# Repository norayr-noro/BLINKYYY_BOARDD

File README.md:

# BLINKYYY_BOARDD
This project is based on the stasis guide on the blinky board, where I mostly followed the guide and changed the final look of the PCB to be a FISH (a FIH if you may):

The circuit is based on the original LED chaser design using a 555 timer IC and a CD4017 decade counter. The LEDs light up sequentially, creating a moving animation around the fish-shaped board. While the electronics stay close to the original tutorial, most of the work went into redesigning the PCB layout and making the board look unique.

# Process

The project, first of all, went through the schematic stage as all projects do. It wasn't anything too interesting. For this project ill be using KiCad.  The guide used a 555 chaser and a 4017 IC, which sounds like random letters and words, but kinda makes sense if you think about it. For example, the 555 timer in this build is kinda the "brain" of the whole build, and as far as I understand, the name comes from the 3x 5K ohm internal resistance, while for the IC unit it would help me connect 10 LED's to the board with ease because it has so many pins (think of it as a "spreader" here). Other than those 2 parts, the other parts in the kit are really simple, like an LED, resistors, a polarized (+ and - differentiate in this one, so be careful when wiring!), and a normal capacitor (don't forget the potentiometer too!!).

After understanding what everything dose the next step was to wire all of them, which wasn't difficult at all, except for the wiring for the 555 timer. For context, the timer has 3 modes:
- Monostable (for time delays) mode, which is usually used as a stopwatch
- Astable Mode, which shifts between high and low
- Bistable Mode, which is like a toggle mode (eg a LED turning on and off with different buttons)
For my build, I followed the Astable mode, which has a bit of a weird wiring, but it wasn't too hard.
Also, usually when routing, I learnt it's better to label wires (by pressing A) so it's easier to understand than to wire everything in one fell swoop.
After all of that, the schematic looks a bit like this:

# The PCB 

Finally, were are onto the PCB designing. Before this, of course you first had to add footprints, obviously. Don't know what they are thinking of symbols and footprints like this, imagine a symbol, something used to understand how a part has to be routed, it's for our case, the symbols are the 555 timer, the IC... everything on the schematic that counts as a part is, and as for footprints Its how the part would look like on the real pcb itself. So I mostly did the same footprints assigning like on the guide this:(+ you will have to download the footprint from [sign in and download](https://app.ultralibrarian.com/details/15b11d40-103f-11e9-ab3a-0a3560a4cccc/Texas-Instruments/CD4017BE]) )

After that, open the PCB designing on KiCad and press F8 or just click update PCB from schematic,  and boom, you're almost done. The next logical step would be to make your own design and place parts and finally route everything, and you're finished (sounds like a lot, but  it's actually not that difficult)
In the PCB, I changed the whole look of it by changing the Edge.Cuts (which are like where the PCB must be cut to get that shape) using the tools on the bottom and middle right. For me, it was in the shape of a Fish...
One of the most interesting parts of this project was adapting the circuit into a non-standard shape. Since the board outline was no longer rectangular, component placement and routing became much more challenging. I had to carefully position LEDs and traces so the board still looked clean while maintaining proper electrical connections.
Finishing off, you usually place the parts on the PCB and route it by placing traces of copper to connect the parts highlighted.

## Tools Used
- KiCad
- GitHub
- JLCPCB
- Hack Club Stasis Guide

## Preview
Here's the final look of the project:
(At the end, I added an extra IC to connect more LED's to make the spiral blinking look cooler and smoother)

## Credits
Original guide and inspiration:
- Hack Club Stasis
- Hack Club Blueprint

Guide used:
https://stasis.hackclub.com/starter-projects/blinky

## Conclusion
Overall this is a perfect project for a begginer to start getting into making these cool custom PCB's and, I really recommend people who start getting into this type of hobby to start from a reallyy easy project like this!Big thanks to [Hack Club Stasis](https://stasis.hackclub.com/starter-projects/blinky?utm_source=chatgpt.com) for the awesome beginner-friendly PCB guide that helped me learn PCB design and customization.

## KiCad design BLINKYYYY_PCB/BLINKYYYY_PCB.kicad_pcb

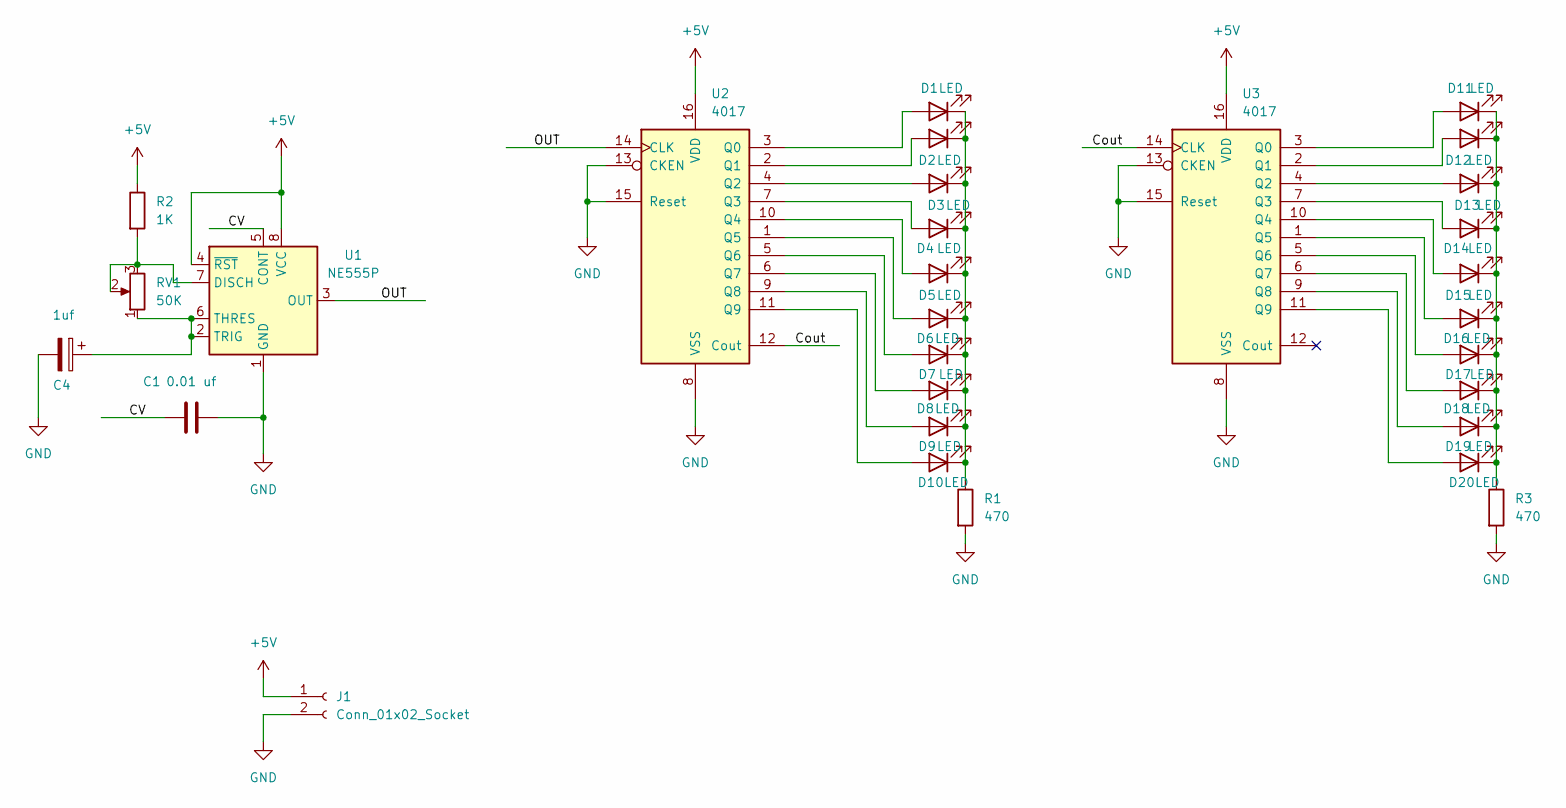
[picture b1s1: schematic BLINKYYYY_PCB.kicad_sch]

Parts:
C1: 0.01 uf; C_Disc_D7.5mm_W2.5mm_P5.00mm
C4: 1uf; CP_Radial_D5.0mm_P2.00mm
D1, D2, D3, D4, D5, D6, D7, D8, D9, D10, D11, D12, D13, D14, D15, D16, D17, D18, D19, D20: LED; LED_D3.0mm
J1: Conn_01x02_Socket; PinHeader_1x02_P2.54mm_Vertical
R1, R3: 470; R_Axial_DIN0207_L6.3mm_D2.5mm_P7.62mm_Horizontal
R2: 1K; R_Axial_DIN0207_L6.3mm_D2.5mm_P7.62mm_Horizontal
RV1: 50K; Potentiometer_Vishay_T93YA_Vertical
U1: NE555P; DIP-8_W7.62mm
U2, U3: 4017; N16

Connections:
+5V: J1.1, R2.1, U1.4 (~RST), U1.8 (VCC), U2.16 (VDD), U3.16 (VDD)
/CV: C1.1, U1.5 (CONT)
/Cout: U2.12 (Cout), U3.14 (CLK)
/OUT: U1.3 (OUT), U2.14 (CLK)
GND: C1.2, C4.2, J1.2, R1.2, R3.2, U1.1 (GND), U2.8 (VSS), U2.13 (CKEN), U2.15 (Reset), U3.8 (VSS), U3.13 (CKEN), U3.15 (Reset)
unnamed: D1.2 (A), U2.3 (Q0)
unnamed: D1.1 (K), D2.1 (K), D3.1 (K), D4.1 (K), D5.1 (K), D6.1 (K), D7.1 (K), D8.1 (K), D9.1 (K), D10.1 (K), R1.1
unnamed: D2.2 (A), U2.2 (Q1)
unnamed: D3.2 (A), U2.4 (Q2)
unnamed: D4.2 (A), U2.7 (Q3)
unnamed: D5.2 (A), U2.10 (Q4)
unnamed: D6.2 (A), U2.1 (Q5)
unnamed: D7.2 (A), U2.5 (Q6)
unnamed: D8.2 (A), U2.6 (Q7)
unnamed: D9.2 (A), U2.9 (Q8)
unnamed: D10.2 (A), U2.11 (Q9)
unnamed: D11.2 (A), U3.3 (Q0)
unnamed: D11.1 (K), D12.1 (K), D13.1 (K), D14.1 (K), D15.1 (K), D16.1 (K), D17.1 (K), D18.1 (K), D19.1 (K), D20.1 (K), R3.1
unnamed: D12.2 (A), U3.2 (Q1)
unnamed: D13.2 (A), U3.4 (Q2)
unnamed: D14.2 (A), U3.7 (Q3)
unnamed: D15.2 (A), U3.10 (Q4)
unnamed: D16.2 (A), U3.1 (Q5)
unnamed: D17.2 (A), U3.5 (Q6)
unnamed: D18.2 (A), U3.6 (Q7)
unnamed: D19.2 (A), U3.9 (Q8)
unnamed: D20.2 (A), U3.11 (Q9)
unnamed: R2.2, RV1.2, RV1.3, U1.7 (DISCH)
unnamed: C4.1, RV1.1, U1.2 (TRIG), U1.6 (THRES)

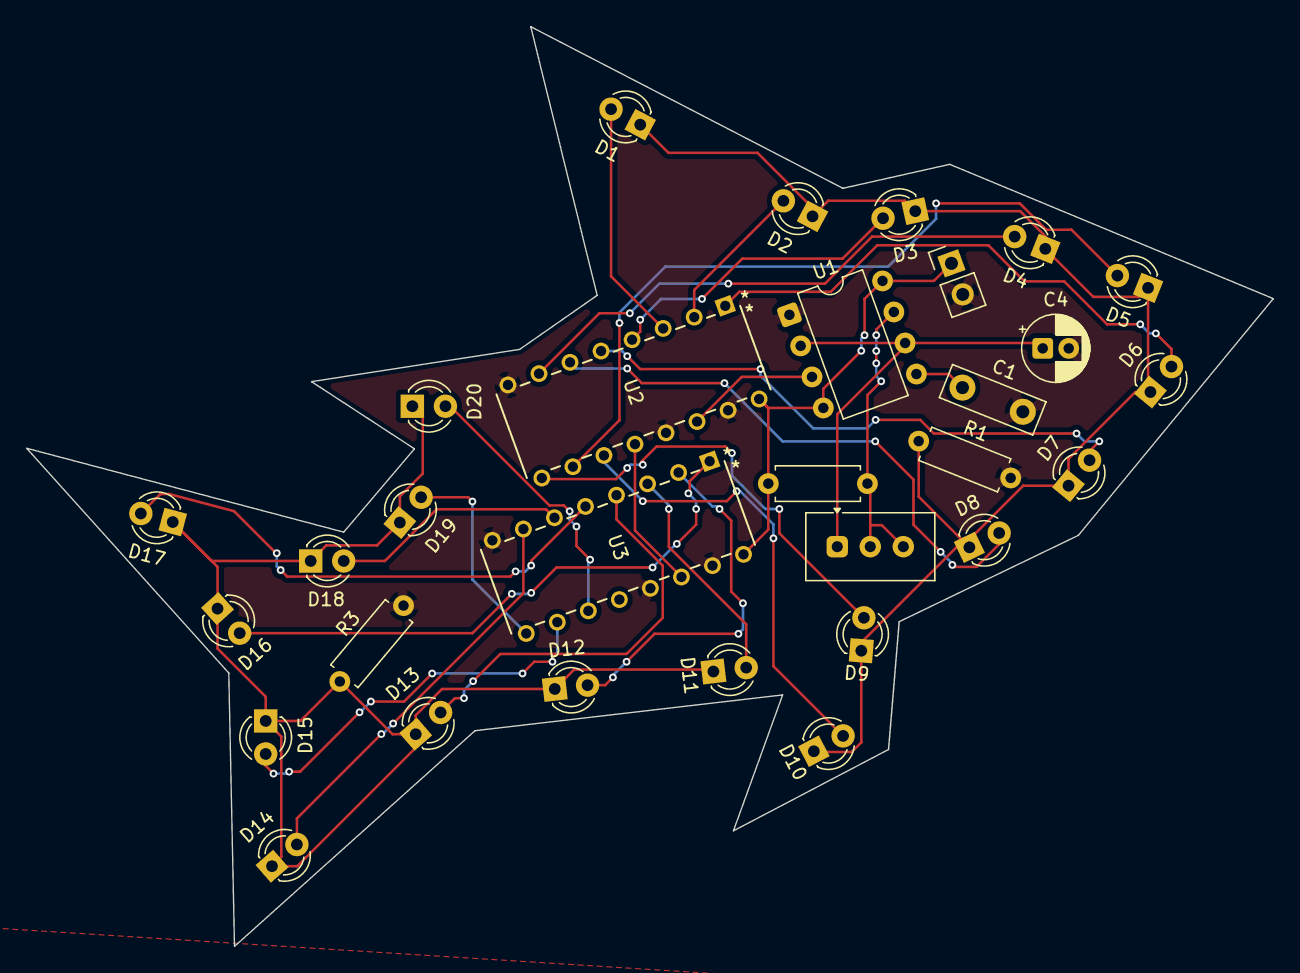
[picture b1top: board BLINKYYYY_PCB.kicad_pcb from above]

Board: 2 copper layers, 95.9 x 70.7 mm, 30 parts (0 on the bottom side), 29 nets.

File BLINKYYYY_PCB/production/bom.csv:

Designator,Footprint,Quantity,Value,LCSC Part #
C1,C_Disc_D7.5mm_W2.5mm_P5.00mm,1,0.01 uf,
C4,CP_Radial_D5.0mm_P2.00mm,1,1uf,
"D1, D10, D11, D12, D13, D14, D15, D16, D17, D18, D19, D2, D20, D3, D4, D5, D6, D7, D8, D9",LED_D3.0mm,20,LED,
J1,PinHeader_1x02_P2.54mm_Vertical,1,Conn_01x02_Socket,
"R1, R3",R_Axial_DIN0207_L6.3mm_D2.5mm_P7.62mm_Horizontal,2,470,
R2,R_Axial_DIN0207_L6.3mm_D2.5mm_P7.62mm_Horizontal,1,1K,
RV1,Potentiometer_Vishay_T93YA_Vertical,1,50K,
U1,DIP-8_W7.62mm,1,NE555P,
"U2, U3",N16,2,4017,

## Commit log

2026-05-10 Revise README with project details and images
    Updated project description to reflect changes and added images.
2026-05-10 Enhance README with project details and process
    Expanded project description, added process details, and included tools used for PCB design. Updated credits and conclusion sections for clarity.
2026-05-12 Delete BLINKYYYY_PCB directory
    deleted directory due to change in pcb
2026-05-12 Update README to enhance project preview section
    Removed duplicate PCB images and added a note about an extra IC for improved LED effects.
